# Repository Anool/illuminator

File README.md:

illuminator
===========

circular LED light illumination ring for ShapeOko Spindle to help light up the work area.

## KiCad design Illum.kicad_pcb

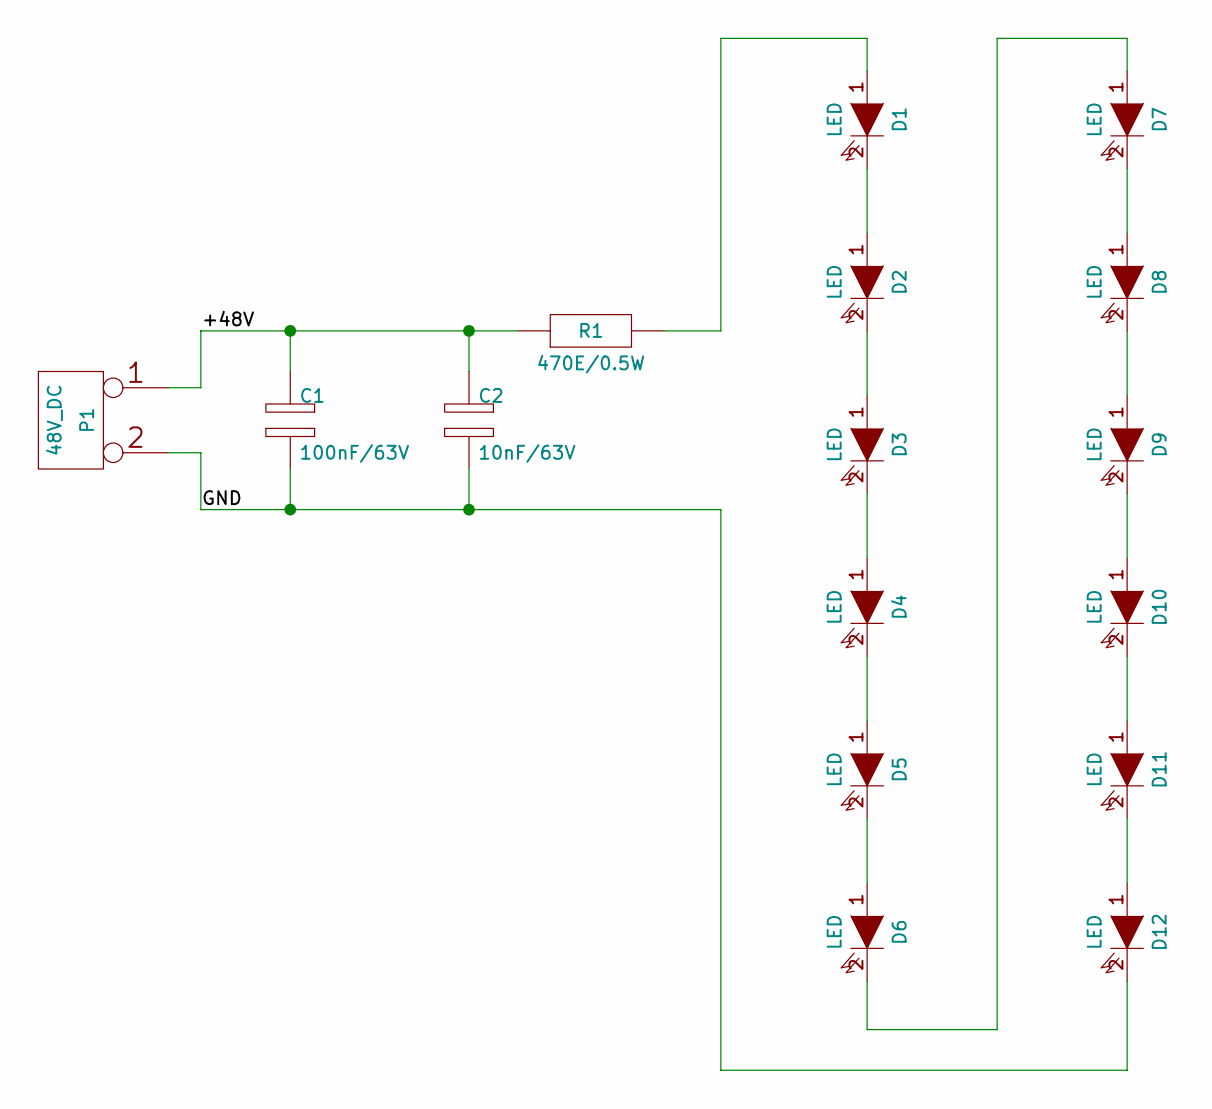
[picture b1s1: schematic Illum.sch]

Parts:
C1: 100nF/63V; SM0805
C2: 10nF/63V; SM0805
D1, D2, D3, D4, D5, D6, D7, D8, D9, D10, D11, D12: LED; LED-5MM
P1: 48V_DC; PIN_ARRAY_2X1
R1: 470E/0.5W; R3

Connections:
/+48V: C1.1, C2.1, P1.1, R1.1
/GND: C1.2, C2.2, D12.2 (K), P1.2 (PM)
unnamed: D1.1 (A), R1.2
unnamed: D6.2 (K), D7.1 (A)
unnamed: D11.2 (K), D12.1 (A)
unnamed: D5.2 (K), D6.1 (A)
unnamed: D10.2 (K), D11.1 (A)
unnamed: D8.2 (K), D9.1 (A)
unnamed: D7.2 (K), D8.1 (A)
unnamed: D9.2 (K), D10.1 (A)
unnamed: D4.2 (K), D5.1 (A)
unnamed: D3.2 (K), D4.1 (A)
unnamed: D2.2 (K), D3.1 (A)
unnamed: D1.2 (K), D2.1 (A)

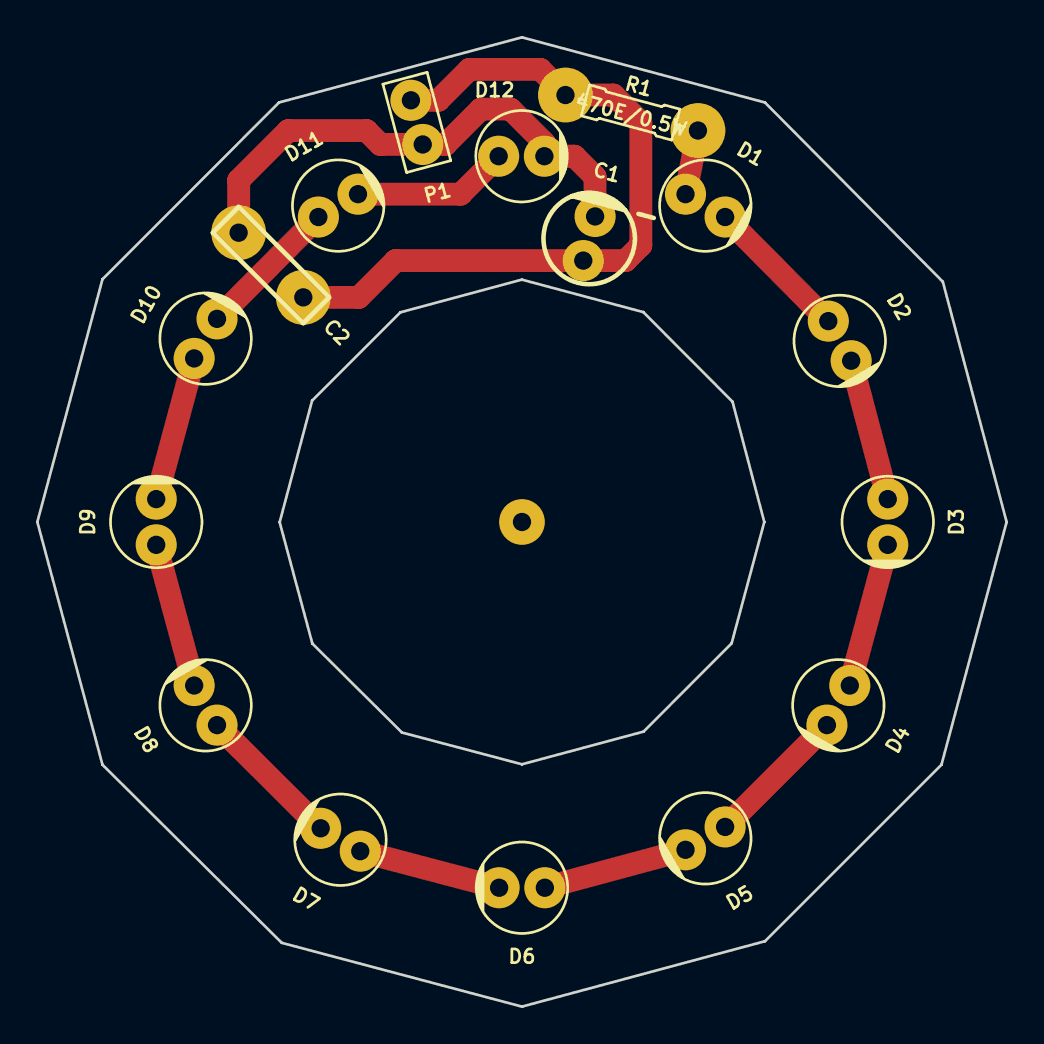
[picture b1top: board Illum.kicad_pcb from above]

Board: 2 copper layers, 53.8 x 53.8 mm, 17 parts (0 on the bottom side), 14 nets.

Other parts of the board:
1pin: VAL**; 1pin

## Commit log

2014-12-21 LED ring light
